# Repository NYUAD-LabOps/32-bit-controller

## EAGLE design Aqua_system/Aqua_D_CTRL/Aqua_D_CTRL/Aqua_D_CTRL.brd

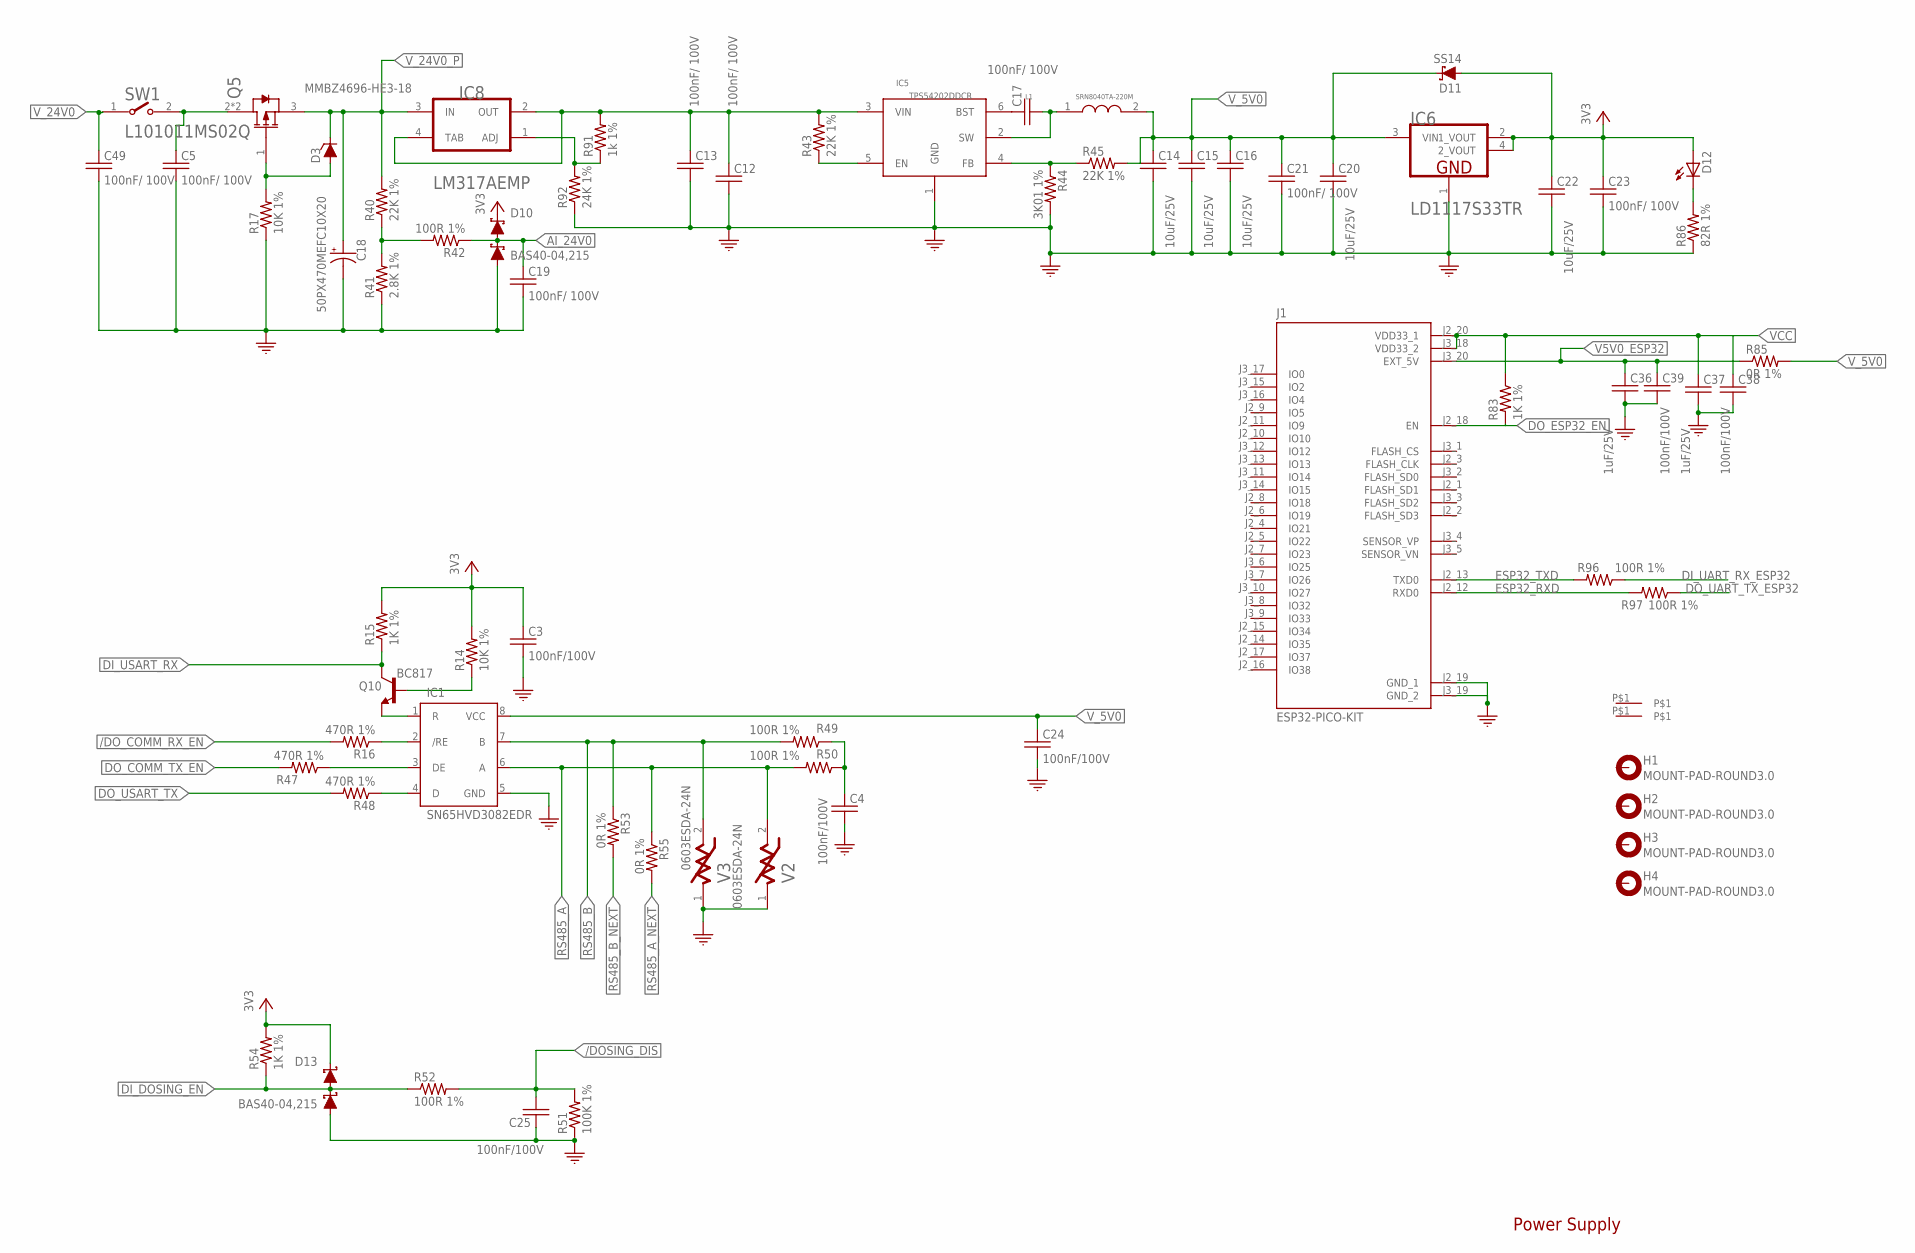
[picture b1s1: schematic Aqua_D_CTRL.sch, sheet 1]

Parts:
C3, C4, C24, C25, C38, C39: 100nF/100V; 0603
C5, C12, C13, C17, C19, C21, C23, C49: 100nF/ 100V; 0603
C14, C15, C16, C20, C22: 10uF/25V; 0603
C18: 50PX470MEFC10X20; CAPACITOR-ELKO-RM5-10X16
C36, C37: 1uF/25V; 0603
D3: MMBZ4696-HE3-18; SOT23-3
D10, D13: BAS40-04,215; SOT23-3
D11: SS14; SMA
D12: 26-21/GPC-F3138B/CA; SMD1206-LED
FID1, FID2: FIDUCIAL
H1, H2, H3, H4: MOUNT-PAD-ROUND3.0; 3,0-PAD
IC1: SN65HVD3082EDR; SOIC8
IC5: TPS54202DDCR; SOT23-6
IC6: LD1117S33TR; SOT223_LD1117S33TR
IC8: LM317AEMP; SOT223_LM317AEMP
J1: ESP32-PICO-KIT; XCVR_ESP32-PICO-KIT
L1: SRN8040TA-220M
Q5: DMP6185SEQ-13; SOT223
Q10: BC817; SOT23
R14, R17: 10K 1%; R0603
R15, R83: 1K 1%; R0603
R16, R47, R48: 470R 1%; R0603
R40, R43, R45: 22K 1%; R0603
R41: 2.8K 1%; R0603
R42, R49, R50, R52, R96, R97: 100R 1%; R0603
R44: 3K01 1%; R0603
R51: 100K 1%; R1206
R53, R55: 0R 1%; R0603
R54: 1K 1%; R1206
R85: 0R 1%; R1206
R86: 82R 1%; R1206
R91: 1k 1%; R0603
R92: 24K 1%; R0603
SW1: L101011MS02Q
V2, V3: 0603ESDA-24N; 0603

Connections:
/DOSING_DIS: C25.2, R51.2, R52.2; also elsewhere on the board
/DO_COMM_RX_EN: R16.2; also elsewhere on the board
AI_24V0: C19.1, D10.3 (C1_A2), R42.1; also elsewhere on the board
DI_DOSING_EN: D13.3 (C1_A2), R52.1, R54.1; also elsewhere on the board
DI_UART_RX_ESP32: R96.1; also elsewhere on the board
DI_USART_RX: Q10.3 (C), R15.1; also elsewhere on the board
DO_COMM_TX_EN: R47.2; also elsewhere on the board
DO_ESP32_EN: J1.J2_18 (EN), R83.2; also elsewhere on the board
DO_UART_TX_ESP32: R97.1; also elsewhere on the board
DO_USART_TX: R48.2; also elsewhere on the board
ESP32_RXD: J1.J2_12 (RXD0), R97.2
ESP32_TXD: J1.J2_13 (TXD0), R96.2
GND: C3.2, C4.2, C5.2, C12.2, C13.2, C14.2, C15.2, C16.2, C18.2 (-), C19.2, C20.2, C21.2, C22.2, C23.2, C24.2, C25.1, C36.2, C37.2, C38.2, C39.2, C49.2, D10.1 (A1), D13.1 (A1), IC1.5 (GND), IC5.1 (GND), IC6.1 (GND), J1.J2_19 (GND_1), J1.J3_19 (GND_2), R17.1, R41.1, R44.2, R51.1, R86.1, R92.1, V2.1, V3.1; also elsewhere on the board
unnamed: C5.1, Q5.2 (DRAIN), Q5.4 (DRAIN), SW1.2
unnamed: Q10.1 (B), R14.1
unnamed: C12.1, C13.1, IC5.3 (VIN), IC8.2 (OUT), IC8.4 (TAB), R43.2, R91.2
unnamed: D3.1 (A), Q5.1 (GATE), R17.2
unnamed: IC8.1 (ADJ), R91.1, R92.2
unnamed: R40.1, R41.2, R42.2
unnamed: IC1.1 (R), Q10.2 (E)
unnamed: C17.2, IC5.2 (SW), L1.1
unnamed: IC1.2 (/RE), R16.1
unnamed: IC5.5 (EN), R43.1
unnamed: IC5.4 (FB), R44.1, R45.1
unnamed: C17.1, IC5.6 (BST)
unnamed: IC1.3 (DE), R47.1
unnamed: IC1.4 (D), R48.1
unnamed: C4.1, R49.1, R50.1
unnamed: D12.2 (C), R86.2
RS485_A: IC1.6 (A), R50.2, R55.1, V2.2; also elsewhere on the board
RS485_A_NEXT: R55.2; also elsewhere on the board
RS485_B: IC1.7 (B), R49.2, R53.1, V3.2; also elsewhere on the board
RS485_B_NEXT: R53.2; also elsewhere on the board
V5V0_ESP32: C36.1, C39.1, J1.J3_20 (EXT_5V), R85.1
VCC: C3.1, C22.1, C23.1, C37.1, C38.1, D10.2 (C2), D11.2 (A), D12.1 (A), D13.2 (C2), IC6.2 (1_VOUT), IC6.4 (2_VOUT), J1.J2_20 (VDD33_1), J1.J3_18 (VDD33_2), R14.2, R15.2, R54.2, R83.1; also elsewhere on the board
V_5V0: C14.1, C15.1, C16.1, C20.1, C21.1, C24.1, D11.1 (C), IC1.8 (VCC), IC6.3 (VIN), L1.2, R45.2, R85.2; also elsewhere on the board
V_24V0: C49.1, SW1.1; also elsewhere on the board
V_24V0_P: C18.1 (+), D3.3 (C), IC8.3 (IN), Q5.3 (SOURCE), R40.2; also elsewhere on the board

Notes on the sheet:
Power Supply

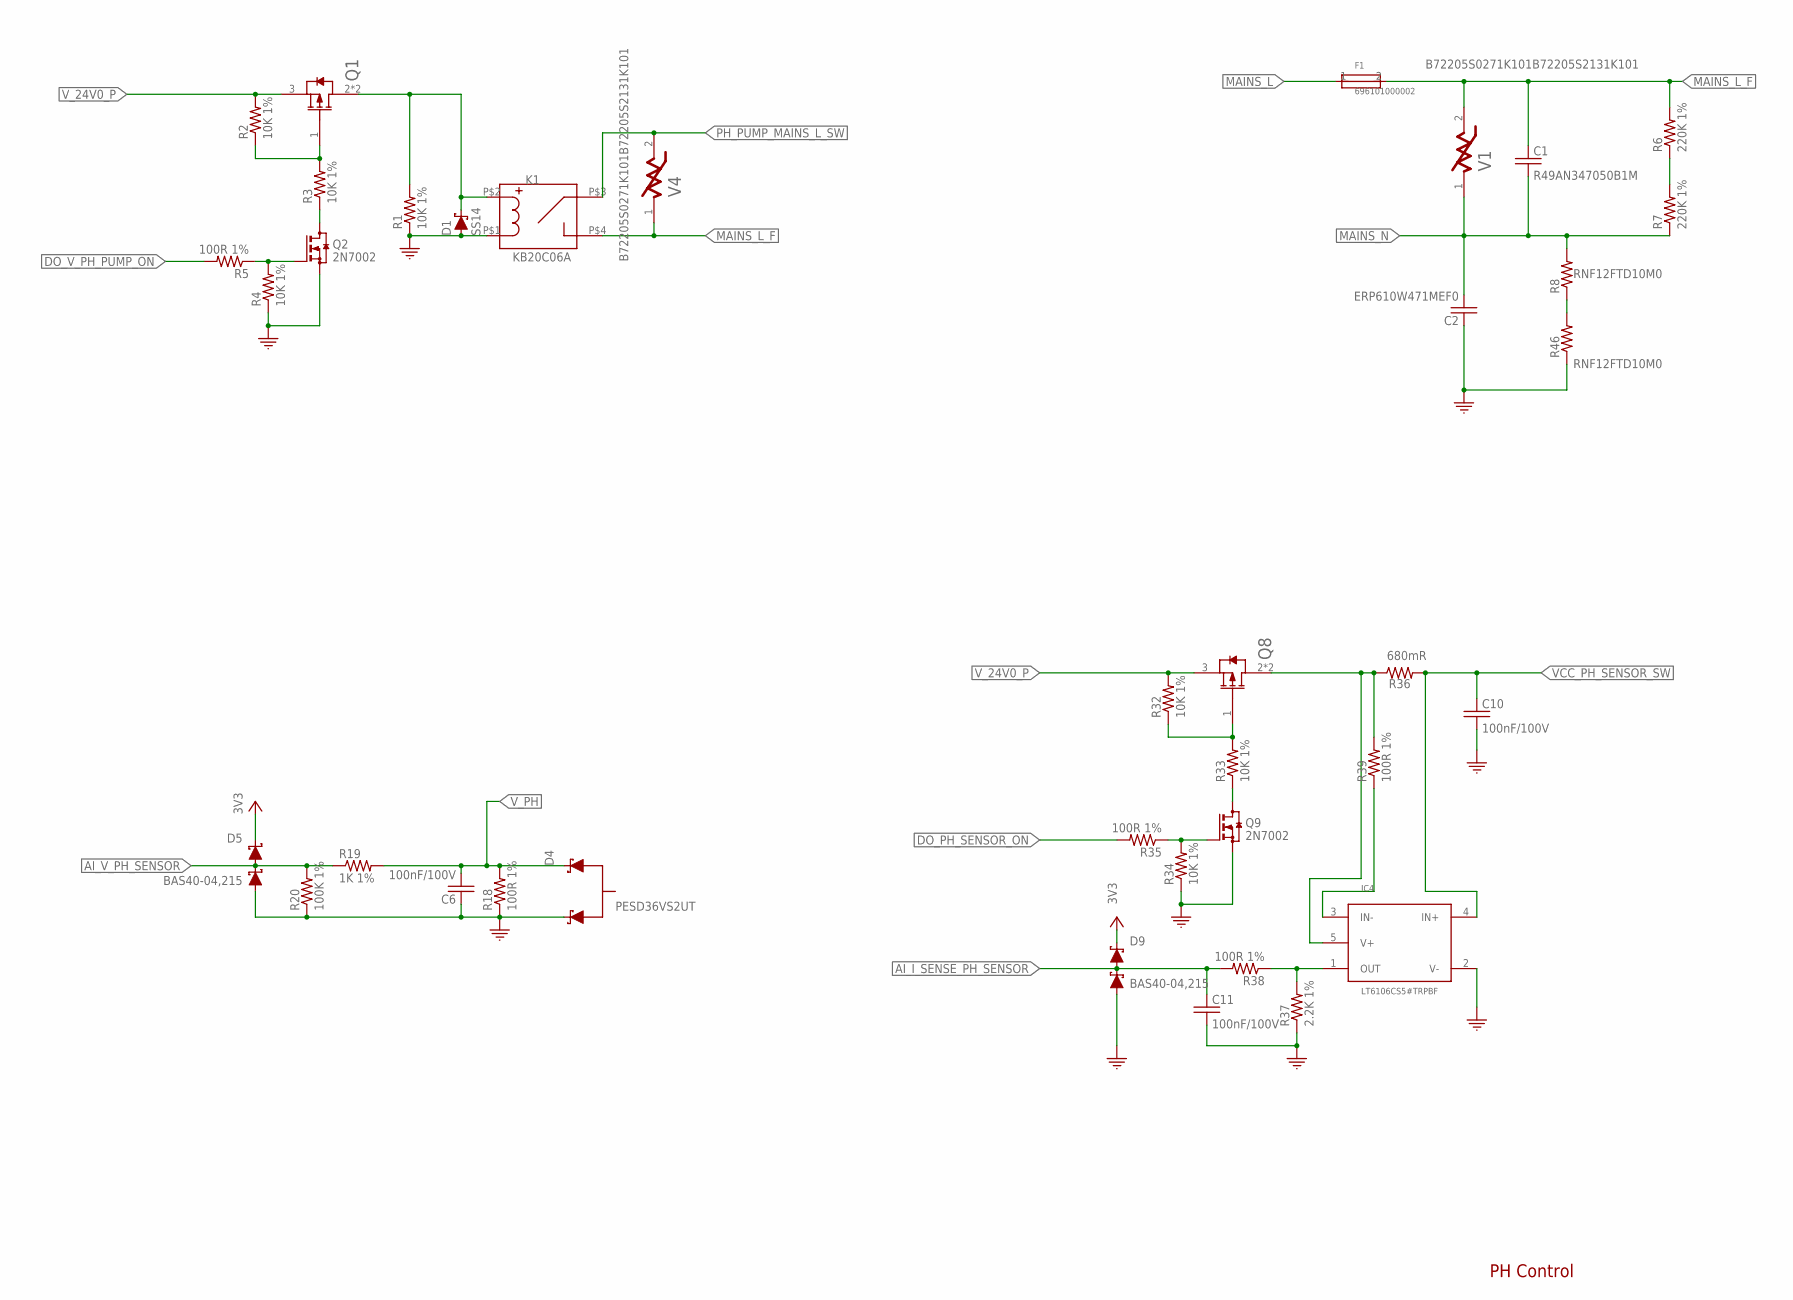
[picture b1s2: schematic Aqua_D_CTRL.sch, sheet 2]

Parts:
C1: R49AN347050B1M
C2: ERP610W471MEF0; CAP-P12.5-H15-W4-D1
C6: 100nF/100V; 0603
C10, C11: 100nF/100V; 0603; PART_VALUE 100nF/100V
D1: SS14; SMA
D4: PESD36VS2UT; SOT23-3
D5, D9: BAS40-04,215; SOT23-3
F1: 696101000002; FUSE_RM22.6
IC4: LT6106CS5#TRPBF; SOT-23-5
K1: KB20C06A; RELAY_KYOTO_KF0604D
Q1, Q8: DMP6185SEQ-13; SOT223
Q2, Q9: 2N7002; SOT23
R1, R2, R3, R4, R32, R33, R34: 10K 1%; 0603
R5, R35, R38, R39: 100R 1%; 0603
R6, R7: 220K 1%; R2010
R8, R46: RNF12FTD10M0; RES-RM12.5-VR37
R18: 100R 1%; R1206
R19: 1K 1%; R0603
R20: 100K 1%; R0603
R36: R_2010; R2010; PART_VALUE 680mR
R37: 2.2K 1%; 0603
V1, V4: B72205S0271K101B72205S2131K101; EPCOS_B72205S0271K101_0

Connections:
AI_I_SENSE_PH_SENSOR: C11.1, D9.3 (C1_A2), R38.2; also elsewhere on the board
AI_V_PH_SENSOR: D5.3 (C1_A2), R19.1, R20.2; also elsewhere on the board
DO_PH_SENSOR_ON: R35.2; also elsewhere on the board
DO_V_PH_PUMP_ON: R5.2; also elsewhere on the board
GND: C2.P$1 (1), C6.1, C10.2, C11.2, D1.2 (A), D4.1 (C1), D5.1 (A1), D9.1 (A1), IC4.2 (V-), K1.P$1 (1), Q2.2 (S), Q9.2 (S), R1.1, R4.1, R18.1, R20.1, R34.1, R37.1, R46.1; also elsewhere on the board
MAINS_L: F1.1; also elsewhere on the board
MAINS_L_F: C1.1, F1.2, K1.P$4 (4), R6.2, V1.2, V4.1; also elsewhere on the board
MAINS_N: C1.2, C2.P$2 (2), R7.1, R8.2, V1.1; also elsewhere on the board
unnamed: D1.1 (C), K1.P$2 (2), Q1.2 (DRAIN), Q1.4 (DRAIN), R1.2
unnamed: Q1.1 (GATE), R2.1, R3.2
unnamed: R6.1, R7.2
unnamed: Q2.3 (D), R3.1
unnamed: Q2.1 (G), R4.2, R5.1
unnamed: Q8.1 (GATE), R32.1, R33.2
unnamed: Q9.3 (D), R33.1
unnamed: Q9.1 (G), R34.2, R35.1
unnamed: IC4.3 (IN-), R39.1
unnamed: IC4.1 (OUT), R37.2, R38.1
unnamed: IC4.5 (V+), Q8.2 (DRAIN), Q8.4 (DRAIN), R36.1, R39.2
unnamed: R8.1, R46.2
PH_PUMP_MAINS_L_SW: K1.P$3 (3), V4.2; also elsewhere on the board
VCC: D5.2 (C2), D9.2 (C2); also elsewhere on the board
VCC_PH_SENSOR_SW: C10.1, IC4.4 (IN+), R36.2; also elsewhere on the board
V_24V0_P: Q1.3 (SOURCE), Q8.3 (SOURCE), R2.2, R32.2; also elsewhere on the board
V_PH: C6.2, D4.2 (C2), R18.2, R19.2; also elsewhere on the board

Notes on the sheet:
PH Control

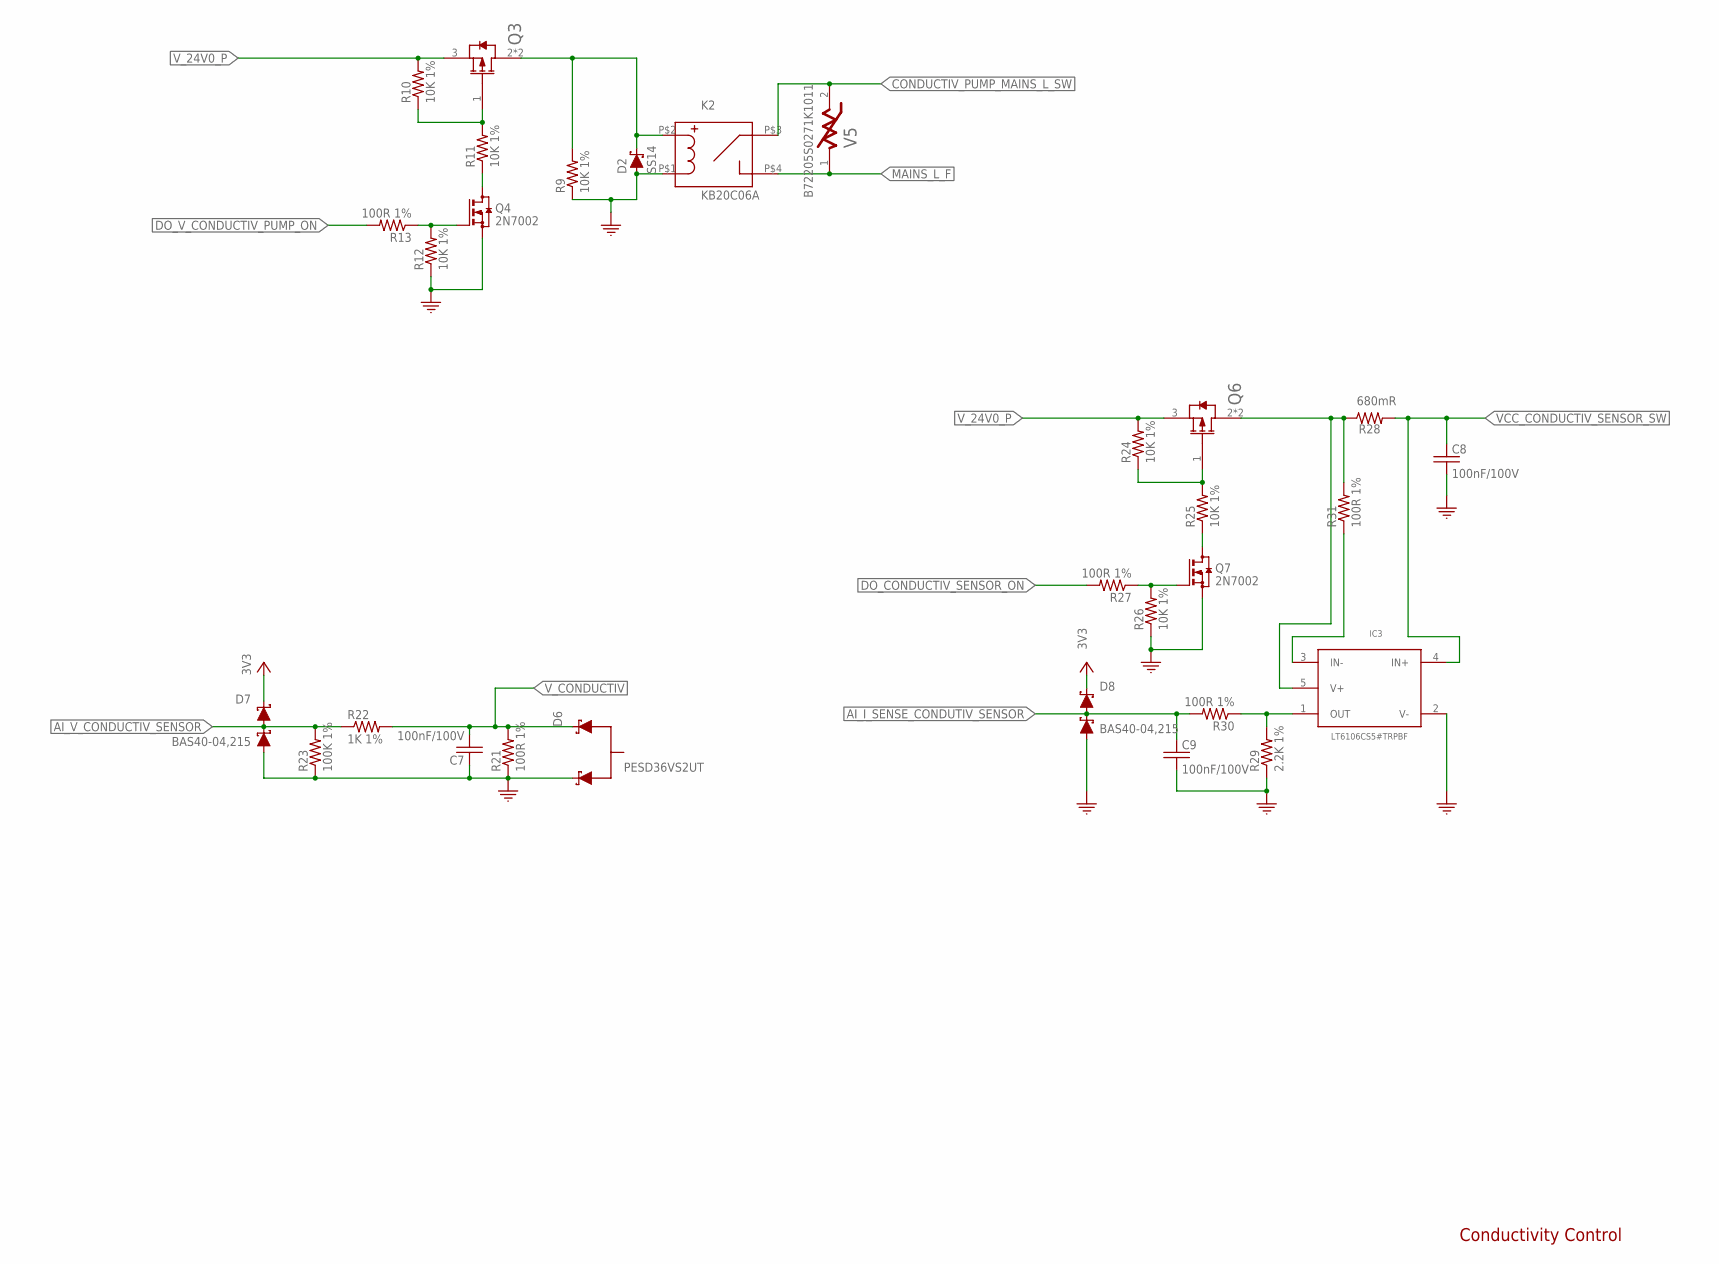
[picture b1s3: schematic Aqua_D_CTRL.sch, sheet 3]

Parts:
C7: 100nF/100V; 0603
C8, C9: 100nF/100V; 0603; PART_VALUE 100nF/100V
D2: SS14; SMA
D6: PESD36VS2UT; SOT23-3
D7, D8: BAS40-04,215; SOT23-3
IC3: LT6106CS5#TRPBF; SOT-23-5
K2: KB20C06A; RELAY_KYOTO_KF0604D
Q3, Q6: DMP6185SEQ-13; SOT223
Q4, Q7: 2N7002; SOT23
R9, R10, R11, R12, R24, R25, R26: 10K 1%; 0603
R13, R27, R30, R31: 100R 1%; 0603
R21: 100R 1%; R1206
R22: 1K 1%; R0603
R23: 100K 1%; R0603
R28: R_2010; R2010; PART_VALUE 680mR
R29: 2.2K 1%; 0603
V5: B72205S0271K1011; EPCOS_B72205S0271K101_MODIFIED

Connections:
AI_I_SENSE_CONDUTIV_SENSOR: C9.1, D8.3 (C1_A2), R30.2; also elsewhere on the board
AI_V_CONDUCTIV_SENSOR: D7.3 (C1_A2), R22.1, R23.2; also elsewhere on the board
CONDUCTIV_PUMP_MAINS_L_SW: K2.P$3 (3), V5.2; also elsewhere on the board
DO_CONDUCTIV_SENSOR_ON: R27.2; also elsewhere on the board
DO_V_CONDUCTIV_PUMP_ON: R13.2; also elsewhere on the board
GND: C7.1, C8.2, C9.2, D2.2 (A), D6.1 (C1), D7.1 (A1), D8.1 (A1), IC3.2 (V-), K2.P$1 (1), Q4.2 (S), Q7.2 (S), R9.1, R12.1, R21.1, R23.1, R26.1, R29.1; also elsewhere on the board
MAINS_L_F: K2.P$4 (4), V5.1; also elsewhere on the board
unnamed: D2.1 (C), K2.P$2 (2), Q3.2 (DRAIN), Q3.4 (DRAIN), R9.2
unnamed: IC3.3 (IN-), R31.1
unnamed: Q3.1 (GATE), R10.1, R11.2
unnamed: Q4.3 (D), R11.1
unnamed: Q6.1 (GATE), R24.1, R25.2
unnamed: Q4.1 (G), R12.2, R13.1
unnamed: Q7.3 (D), R25.1
unnamed: Q7.1 (G), R26.2, R27.1
unnamed: IC3.1 (OUT), R29.2, R30.1
unnamed: IC3.5 (V+), Q6.2 (DRAIN), Q6.4 (DRAIN), R28.1, R31.2
VCC: D7.2 (C2), D8.2 (C2); also elsewhere on the board
VCC_CONDUCTIV_SENSOR_SW: C8.1, IC3.4 (IN+), R28.2; also elsewhere on the board
V_24V0_P: Q3.3 (SOURCE), Q6.3 (SOURCE), R10.2, R24.2; also elsewhere on the board
V_CONDUCTIV: C7.2, D6.2 (C2), R21.2, R22.2; also elsewhere on the board

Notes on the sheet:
Conductivity Control

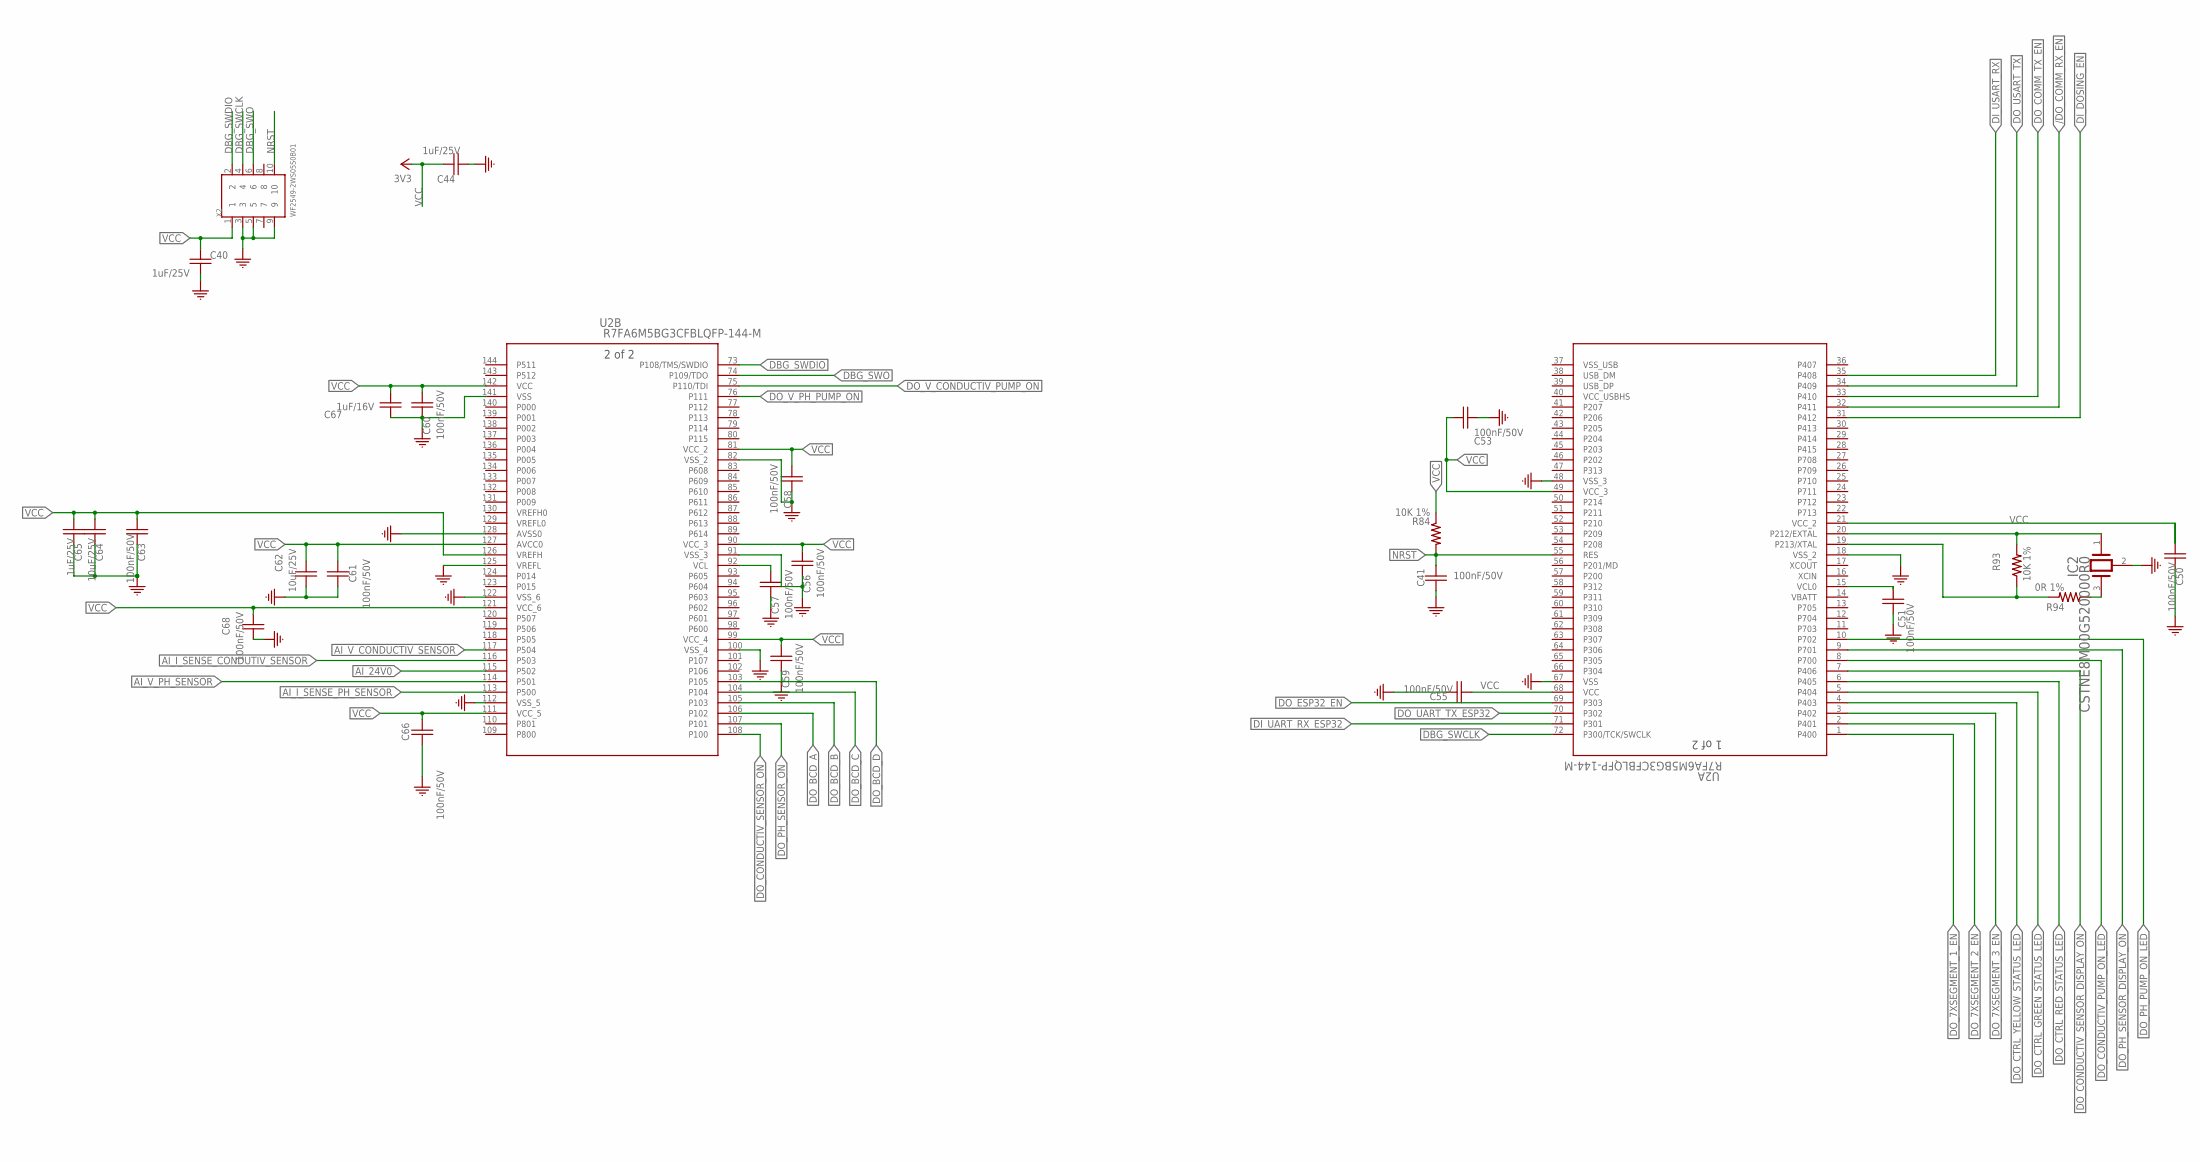
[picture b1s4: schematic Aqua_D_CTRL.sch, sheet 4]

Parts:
C40, C44, C65: 1uF/25V; 0603
C41, C50, C51, C53, C55, C56, C57, C58, C59, C60, C61, C63, C66, C68: 100nF/50V; 0603
C62, C64: 10uF/25V; 0603
C67: 1uF/16V; 0603
IC2: CSTNE8M00G520000R0
R84, R93: 10K 1%; R0603
R94: 0R 1%; R0603
U2: R7FA6M5BG3CFBLQFP-144-M; LQFP-144-M
X2: WF2549-2WS05S0B01; X10_100MIL_2XROW_VERT

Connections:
/DO_COMM_RX_EN: U2.32 (P411); also elsewhere on the board
AI_24V0: U2.115 (P502); also elsewhere on the board
AI_I_SENSE_CONDUTIV_SENSOR: U2.116 (P503); also elsewhere on the board
AI_I_SENSE_PH_SENSOR: U2.113 (P500); also elsewhere on the board
AI_V_CONDUCTIV_SENSOR: U2.117 (P504); also elsewhere on the board
AI_V_PH_SENSOR: U2.114 (P501); also elsewhere on the board
DBG_SWCLK: U2.72 (P300/TCK/SWCLK), X2.4
DBG_SWDIO: U2.73 (P108/TMS/SWDIO), X2.2
DBG_SWO: U2.74 (P109/TDO), X2.6
DI_DOSING_EN: U2.31 (P412); also elsewhere on the board
DI_UART_RX_ESP32: U2.71 (P301); also elsewhere on the board
DI_USART_RX: U2.35 (P408); also elsewhere on the board
DO_7XSEGMENT_1_EN: U2.1 (P400); also elsewhere on the board
DO_7XSEGMENT_2_EN: U2.2 (P401); also elsewhere on the board
DO_7XSEGMENT_3_EN: U2.3 (P402); also elsewhere on the board
DO_BCD_A: U2.106 (P102); also elsewhere on the board
DO_BCD_B: U2.105 (P103); also elsewhere on the board
DO_BCD_C: U2.104; also elsewhere on the board
DO_BCD_D: U2.103 (P105); also elsewhere on the board
DO_COMM_TX_EN: U2.33 (P410); also elsewhere on the board
DO_CONDUCTIV_PUMP_ON_LED: U2.8 (P700); also elsewhere on the board
DO_CONDUCTIV_SENSOR_DISPLAY_ON: U2.7 (P406); also elsewhere on the board
DO_CONDUCTIV_SENSOR_ON: U2.108 (P100); also elsewhere on the board
DO_CTRL_GREEN_STATUS_LED: U2.5 (P404); also elsewhere on the board
DO_CTRL_RED_STATUS_LED: U2.6 (P405); also elsewhere on the board
DO_CTRL_YELLOW_STATUS_LED: U2.4 (P403); also elsewhere on the board
DO_ESP32_EN: U2.69 (P303); also elsewhere on the board
DO_PH_PUMP_ON_LED: U2.10 (P702); also elsewhere on the board
DO_PH_SENSOR_DISPLAY_ON: U2.9 (P701); also elsewhere on the board
DO_PH_SENSOR_ON: U2.107 (P101); also elsewhere on the board
DO_UART_TX_ESP32: U2.70 (P302); also elsewhere on the board
DO_USART_TX: U2.34 (P409); also elsewhere on the board
DO_V_CONDUCTIV_PUMP_ON: U2.75 (P110/TDI); also elsewhere on the board
DO_V_PH_PUMP_ON: U2.76 (P111); also elsewhere on the board
GND: C40.2, C41.2, C44.2, C50.1, C51.1, C53.1, C55.1, C56.1, C57.1, C58.1, C59.1, C60.1, C61.1, C62.1, C63.1, C64.1, C65.1, C66.1, C67.1, C68.1, IC2.2 (GND), U2.18 (VSS_2), U2.48 (VSS_3), U2.67 (VSS), U2.82 (VSS_2), U2.91 (VSS_3), U2.100 (VSS_4), U2.112 (VSS_5), U2.122 (VSS_6), U2.125 (VREFL), U2.128 (AVSS0), U2.141 (VSS), X2.3, X2.5, X2.9; also elsewhere on the board
unnamed: IC2.3 (OUTPUT), R94.1
unnamed: R93.1, R94.2, U2.19 (P213/XTAL)
unnamed: C51.2, U2.15 (VCL0)
unnamed: IC2.1 (INPUT), R93.2, U2.20 (P212/EXTAL)
unnamed: C57.2, U2.92 (VCL)
NRST: C41.1, R84.2, U2.55 (RES), X2.10
VBATT: U2.14 (VBATT)
VCC: C40.1, C44.1, C50.2, C53.2, C55.2, C56.2, C58.2, C59.2, C60.2, C61.2, C62.2, C63.2, C64.2, C65.2, C66.2, C67.2, C68.2, R84.1, U2.21 (VCC_2), U2.49 (VCC_3), U2.68 (VCC), U2.81 (VCC_2), U2.90 (VCC_3), U2.99 (VCC_4), U2.111 (VCC_5), U2.121 (VCC_6), U2.126 (VREFH), U2.127 (AVCC0), U2.142 (VCC), X2.1; also elsewhere on the board
VCC_USBHS: U2.40 (VCC_USBHS)
VREFH0: U2.130 (VREFH0)
VREFL0: U2.129 (VREFL0)
VSS_USB: U2.37 (VSS_USB)

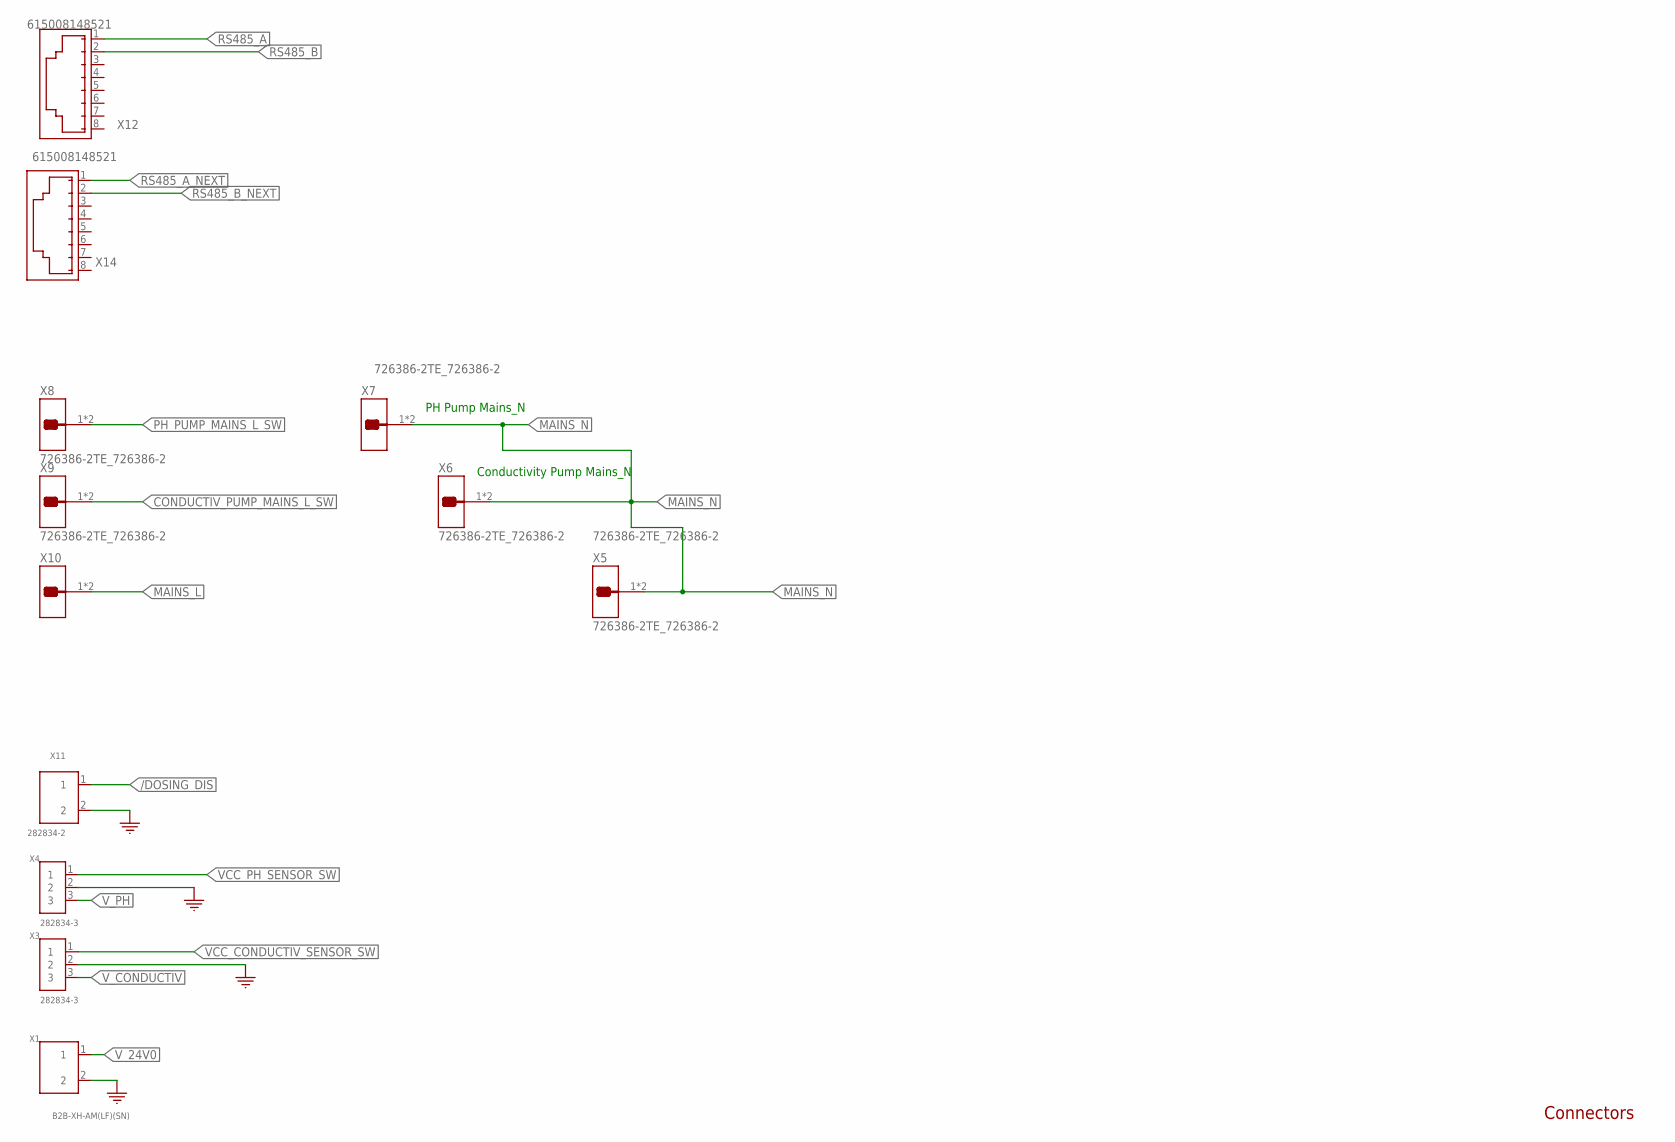
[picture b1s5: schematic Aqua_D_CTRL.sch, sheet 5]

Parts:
X1: B2B-XH-AM(LF)(SN)
X3, X4: 282834-3; TE_282834-3_0
X5, X6, X7, X8, X9, X10: 726386-2TE_726386-2; TE_726386-2
X11: 282834-2; TE_282834-2_0
X12, X14: 615008148521

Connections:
/DOSING_DIS: X11.1; also elsewhere on the board
CONDUCTIV_PUMP_MAINS_L_SW: X9.1, X9.1-2; also elsewhere on the board
GND: X1.2, X3.2, X4.2, X11.2; also elsewhere on the board
MAINS_L: X10.1, X10.1-2; also elsewhere on the board
MAINS_N: X5.1, X5.1-2, X6.1, X6.1-2, X7.1, X7.1-2; also elsewhere on the board
PH_PUMP_MAINS_L_SW: X8.1, X8.1-2; also elsewhere on the board
RS485_A: X12.1; also elsewhere on the board
RS485_A_NEXT: X14.1; also elsewhere on the board
RS485_B: X12.2; also elsewhere on the board
RS485_B_NEXT: X14.2; also elsewhere on the board
VCC_CONDUCTIV_SENSOR_SW: X3.1; also elsewhere on the board
VCC_PH_SENSOR_SW: X4.1; also elsewhere on the board
V_24V0: X1.1; also elsewhere on the board
V_CONDUCTIV: X3.3; also elsewhere on the board
V_PH: X4.3; also elsewhere on the board

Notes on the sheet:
Connectors
Conductivity Pump Mains_N
PH Pump Mains_N

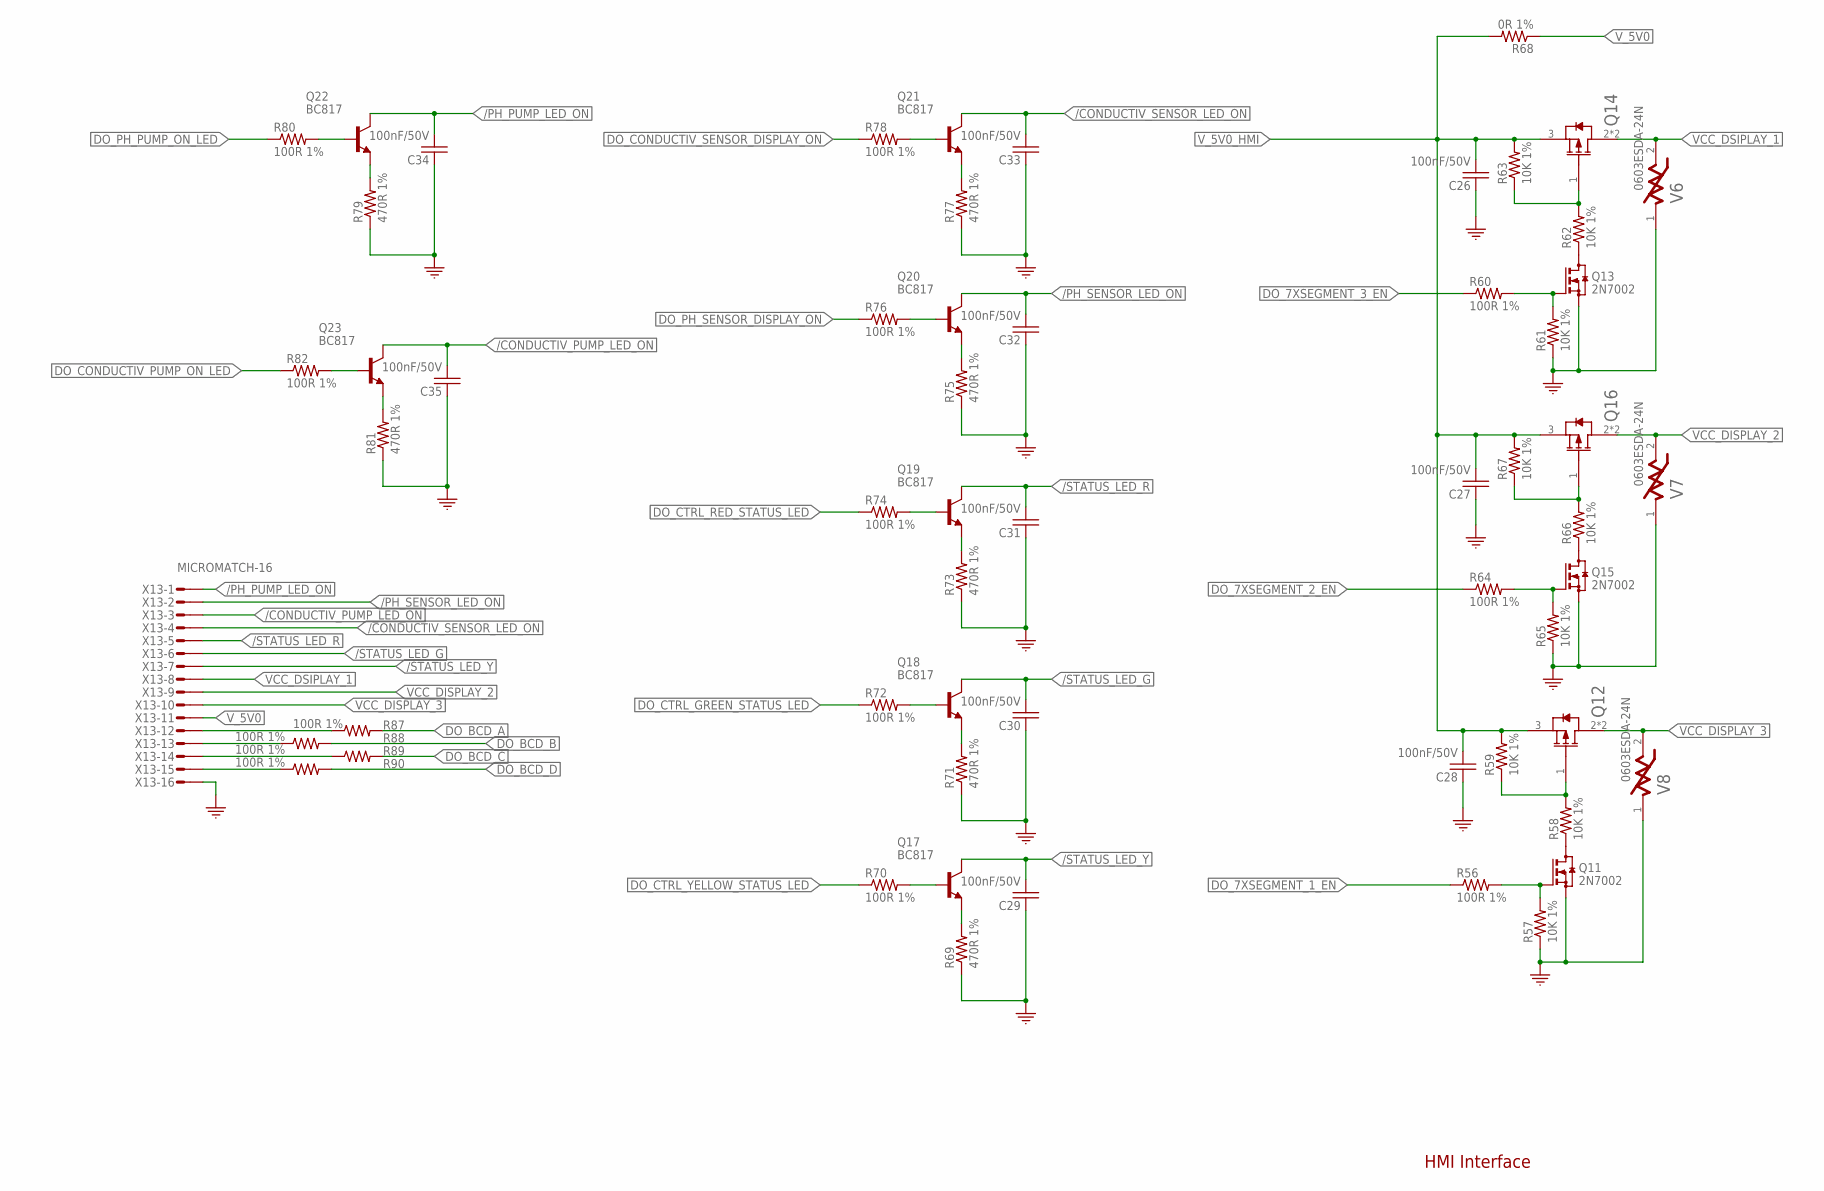
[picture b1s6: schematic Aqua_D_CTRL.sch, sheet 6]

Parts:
C26, C27, C28, C29, C30, C31, C32, C33, C34, C35: 100nF/50V; 0603
Q11, Q13, Q15: 2N7002; SOT23
Q12, Q14, Q16: DMP6185SEQ-13; SOT223
Q17, Q18, Q19, Q20, Q21, Q22, Q23: BC817; SOT23
R56, R60, R64, R70, R72, R74, R76, R78, R80, R82, R87, R88, R89, R90: 100R 1%; R0603
R57, R58, R59, R61, R62, R63, R65, R66, R67: 10K 1%; R0603
R68: 0R 1%; R0603
R69, R71, R73, R75, R77, R79, R81: 470R 1%; R0603
V6, V7, V8: 0603ESDA-24N; 0603
X13: MICROMATCH-16

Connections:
/CONDUCTIV_PUMP_LED_ON: C35.2, Q23.3 (C), X13.3
/CONDUCTIV_SENSOR_LED_ON: C33.2, Q21.3 (C), X13.4
/PH_PUMP_LED_ON: C34.2, Q22.3 (C), X13.1
/PH_SENSOR_LED_ON: C32.2, Q20.3 (C), X13.2
/STATUS_LED_G: C30.2, Q18.3 (C), X13.6
/STATUS_LED_R: C31.2, Q19.3 (C), X13.5
/STATUS_LED_Y: C29.2, Q17.3 (C), X13.7
DO_7XSEGMENT_1_EN: R56.1; also elsewhere on the board
DO_7XSEGMENT_2_EN: R64.1; also elsewhere on the board
DO_7XSEGMENT_3_EN: R60.1; also elsewhere on the board
DO_BCD_A: R87.2; also elsewhere on the board
DO_BCD_B: R88.2; also elsewhere on the board
DO_BCD_C: R89.2; also elsewhere on the board
DO_BCD_D: R90.2; also elsewhere on the board
DO_CONDUCTIV_PUMP_ON_LED: R82.1; also elsewhere on the board
DO_CONDUCTIV_SENSOR_DISPLAY_ON: R78.1; also elsewhere on the board
DO_CTRL_GREEN_STATUS_LED: R72.1; also elsewhere on the board
DO_CTRL_RED_STATUS_LED: R74.1; also elsewhere on the board
DO_CTRL_YELLOW_STATUS_LED: R70.1; also elsewhere on the board
DO_PH_PUMP_ON_LED: R80.1; also elsewhere on the board
DO_PH_SENSOR_DISPLAY_ON: R76.1; also elsewhere on the board
GND: C26.1, C27.1, C28.1, C29.1, C30.1, C31.1, C32.1, C33.1, C34.1, C35.1, Q11.2 (S), Q13.2 (S), Q15.2 (S), R57.1, R61.1, R65.1, R69.1, R71.1, R73.1, R75.1, R77.1, R79.1, R81.1, V6.1, V7.1, V8.1, X13.16; also elsewhere on the board
unnamed: R88.1, X13.13
unnamed: Q11.1 (G), R56.2, R57.2
unnamed: Q11.3 (D), R58.1
unnamed: R87.1, X13.12
unnamed: Q12.1 (GATE), R58.2, R59.1
unnamed: R90.1, X13.15
unnamed: Q17.2 (E), R69.2
unnamed: Q17.1 (B), R70.2
unnamed: Q13.1 (G), R60.2, R61.2
unnamed: Q13.3 (D), R62.1
unnamed: Q14.1 (GATE), R62.2, R63.1
unnamed: Q18.2 (E), R71.2
unnamed: Q18.1 (B), R72.2
unnamed: Q15.1 (G), R64.2, R65.2
unnamed: Q15.3 (D), R66.1
unnamed: Q16.1 (GATE), R66.2, R67.1
unnamed: Q19.2 (E), R73.2
unnamed: Q19.1 (B), R74.2
unnamed: R89.1, X13.14
unnamed: Q20.2 (E), R75.2
unnamed: Q20.1 (B), R76.2
unnamed: Q21.2 (E), R77.2
unnamed: Q21.1 (B), R78.2
unnamed: Q22.2 (E), R79.2
unnamed: Q22.1 (B), R80.2
unnamed: Q23.2 (E), R81.2
unnamed: Q23.1 (B), R82.2
VCC_DISPLAY_2: Q16.2 (DRAIN), Q16.4 (DRAIN), V7.2, X13.9
VCC_DISPLAY_3: Q12.2 (DRAIN), Q12.4 (DRAIN), V8.2, X13.10
VCC_DSIPLAY_1: Q14.2 (DRAIN), Q14.4 (DRAIN), V6.2, X13.8
V_5V0: R68.1, X13.11; also elsewhere on the board
V_5V0_HMI: C26.2, C27.2, C28.2, Q12.3 (SOURCE), Q14.3 (SOURCE), Q16.3 (SOURCE), R59.2, R63.2, R67.2, R68.2

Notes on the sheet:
HMI Interface

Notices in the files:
parts and their libraries:
Labops_Lib_AH: COPYRIGHT: Copyright (C) 2022 Ultra Librarian. All rights reserved.
